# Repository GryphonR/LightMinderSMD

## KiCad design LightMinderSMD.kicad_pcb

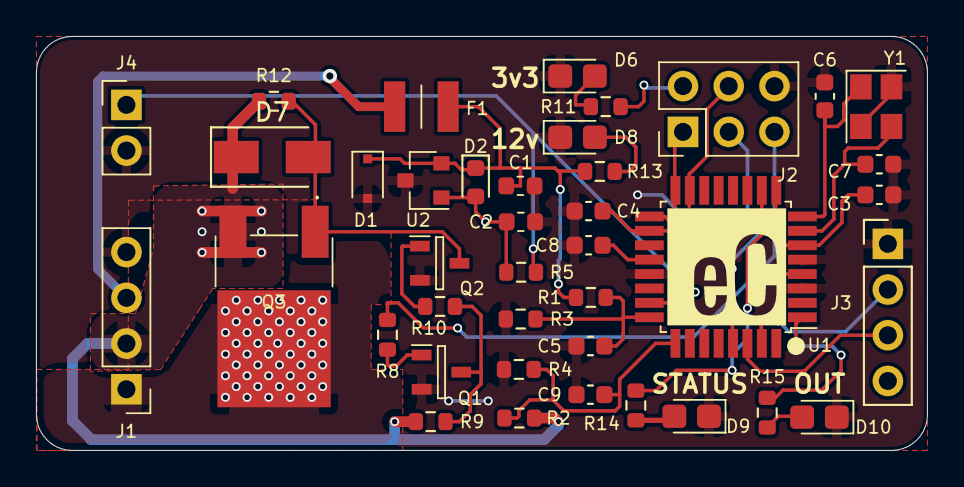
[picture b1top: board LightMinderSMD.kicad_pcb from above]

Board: 2 copper layers, 49.5 x 23.0 mm, 40 parts (0 on the bottom side), 29 nets.

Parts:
C1, C2: 10u; C_0603_1608Metric
C3, C4, C8: 100n; C_0603_1608Metric
C5, C9: 470nF; C_0603_1608Metric
C6, C7: 20p; C_0603_1608Metric
D1: 20v; D_SOD-323F
D2: D_Schottky; D_0603_1608Metric
D6, D8, D9, D10: LED; LED_0805_2012Metric_Castellated
D7: 20v TVS; D_SMA
F1: 1210L020WR; FUSC3226X100N
J1: Conn_01x04_Female; PinHeader_1x04_P2.54mm_Vertical
J2: AVR-ISP-6; PinHeader_2x03_P2.54mm_Vertical
J3: Conn_01x04; PinHeader_1x04_P2.54mm_Vertical
J4: Conn_01x02_Female; PinHeader_1x02_P2.54mm_Vertical
Q1, Q2: Q_NPN_BEC; SOT95P240X115-3N
Q3: STD35P6LLF6
R1, R2: 18k; R_0603_1608Metric
R3, R4: 1.3k; R_0603_1608Metric
R5, R9, R12: 10k; R_0603_1608Metric
R8, R10: 1k; R_0603_1608Metric
R11, R14, R15: 100; R_0603_1608Metric
R13: 750; R_0603_1608Metric
U1: ATmega328P-AU; TQFP-32_7x7mm_P0.8mm
U2: LM3480-3.3; SOT-23
Y1: Crystal_GND24; Crystal_SMD_3225-4Pin_3.2x2.5mm

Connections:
3v3: C2.1, C3.1, C4.1, D2.2 (A), J2.2 (VCC), J3.4, R5.1, R11.1, U1.4 (VCC), U1.6 (VCC), U1.18 (AVCC), U2.1 (VO)
/12vFused: C1.1, D1.1 (K), D2.1 (K), F1.2, R1.1, R13.1, U2.2 (VI)
/Error_LED: R14.1, U1.10 (PD6)
/Light_Out_LED: R15.1, U1.1 (PD3)
/Light_Out_Logic: R8.1, U1.9 (PD5)
/RX: J3.3, U1.30 (PD0)
/Sheet60CB0BEF/MISO: J2.1 (MISO), U1.16 (PB4)
/Sheet60CB0BEF/MOSI: J2.4 (MOSI), U1.15 (PB3)
/Sheet60CB0BEF/Reset: J2.5 (~RST), U1.29 (~RESET/PC6)
/Sheet60CB0BEF/SCK: J2.3 (SCK), U1.17 (PB5)
/Sheet60CB0BEF/XTAL1: C7.1, U1.7 (XTAL1/PB6), Y1.3
/Sheet60CB0BEF/XTAL2: C6.1, U1.8 (XTAL2/PB7), Y1.1
/Sheet60CB0BEF/aref: C8.1, U1.20 (AREF)
/TX: J3.2, U1.31 (PD1)
/batt_voltage_ref: C5.1, R1.2, R3.1, U1.24 (PC1)
/dipped_beam_ref: C9.1, R2.2, R4.1, U1.25 (PC2)
/light_ref: J4.1, R5.2, U1.23 (PC0)
DippedBeam_12v: D7.1 (A1), J1.2, Q3.3, R2.1, R9.1, R12.1
DippedBeam_Out: J1.1, Q3.2
unnamed: D6.2 (A), R11.2
unnamed: D7.2 (A2), Q2.3 (C), Q3.1, R12.2
unnamed: D8.2 (A), R13.2
unnamed: D9.2 (A), R14.2
unnamed: D10.2 (A), R15.2
unnamed: Q1.1 (B), R8.2
unnamed: Q1.3 (C), R9.2, R10.1
unnamed: Q2.1 (B), R10.2
Sidelight_12v: F1.1, J1.3
Sidelight_GND: C1.2, C2.2, C3.2, C4.2, C5.2, C6.2, C7.2, C8.2, C9.2, D1.2 (A), D6.1 (K), D8.1 (K), D9.1 (K), D10.1 (K), J1.4, J2.6 (GND), J3.1, J4.2, Q1.2 (E), Q2.2 (E), R3.2, R4.2, U1.3 (GND), U1.5 (GND), U1.21 (GND), U2.3 (GND), Y1.2, Y1.4

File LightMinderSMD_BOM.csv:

"Id";"Designator";"Package";"Quantity";"Designation";"Supplier and ref";
1;"G***";"lightminder_logo";1;"LOGO";;;
2;"Q3";"STD35P6LLF6";1;"STD35P6LLF6";;;
3;"J3";"PinHeader_1x04_P2.54mm_Vertical";1;"Conn_01x04";;;
4;"J2";"PinHeader_2x03_P2.54mm_Vertical";1;"AVR-ISP-6";;;
5;"D5,D4";"D_SOT-23_ANK";2;"D_Schottky";;;
6;"C9,C5";"C_0201_0603Metric";2;"470nF";;;
7;"J4";"PinHeader_1x02_P2.54mm_Vertical";1;"Conn_01x02_Female";;;
8;"J1";"PinHeader_1x04_P2.54mm_Vertical";1;"Conn_01x04_Female";;;
9;"U2";"SOT-23";1;"LM3480-3.3";;;
10;"R15,R14,R13,R11";"R_0201_0603Metric";4;"R";;;
11;"R12,R9";"R_0402_1005Metric";2;"10k";;;
12;"R10,R8";"R_0402_1005Metric";2;"1k";;;
13;"R5";"R_0201_0603Metric";1;"10k";;;
14;"R2,R1";"R_0201_0603Metric";2;"18k";;;
15;"Q2,Q1";"SOT95P240X115-3N";2;"Q_NPN_BEC";;;
16;"F1";"FUSC3226X100N";1;"1210L020WR";;;
17;"D10,D9,D8,D6";"LED_0805_2012Metric_Castellated";4;"LED";;;
18;"D7";"DO-214ACSMA";1;"20v TVS";;;
19;"C8,C4,C3";"C_0201_0603Metric";3;"100n";;;
20;"C2,C1";"C_0603_1608Metric";2;"10u";;;
21;"Y1";"Crystal_SMD_3225-4Pin_3.2x2.5mm";1;"Crystal_GND24";;;
22;"C7,C6";"C_0201_0603Metric";2;"20p";;;
23;"D1";"D_SOD-323F";1;"20v";;;
24;"R4,R3";"R_0201_0603Metric";2;"1.3k";;;
25;"U1";"TQFP-32_7x7mm_P0.8mm";1;"ATmega328P-AU";;;

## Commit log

2021-11-11 Initial commit, initial design
2021-11-16 Version 2 PCB fully routed, simulations added
2021-11-17 Finalise PCB, add logo and silk text
2021-12-31 Version 0.3 prototype - Manufactured
2022-01-01 Upgrade to 6.0 and add html bom
2022-01-01 Added index.html
2022-01-06 Starting V0.4 Updates
2022-01-06 Updated gitignore, removed kicad v6 backups folder
2022-01-06 Directory cleanup
2022-01-07 Thermal management and Power plane modifications
2022-01-12 Layout Improvements and Added 3D models
2022-01-24 ICSP Typo Fix
